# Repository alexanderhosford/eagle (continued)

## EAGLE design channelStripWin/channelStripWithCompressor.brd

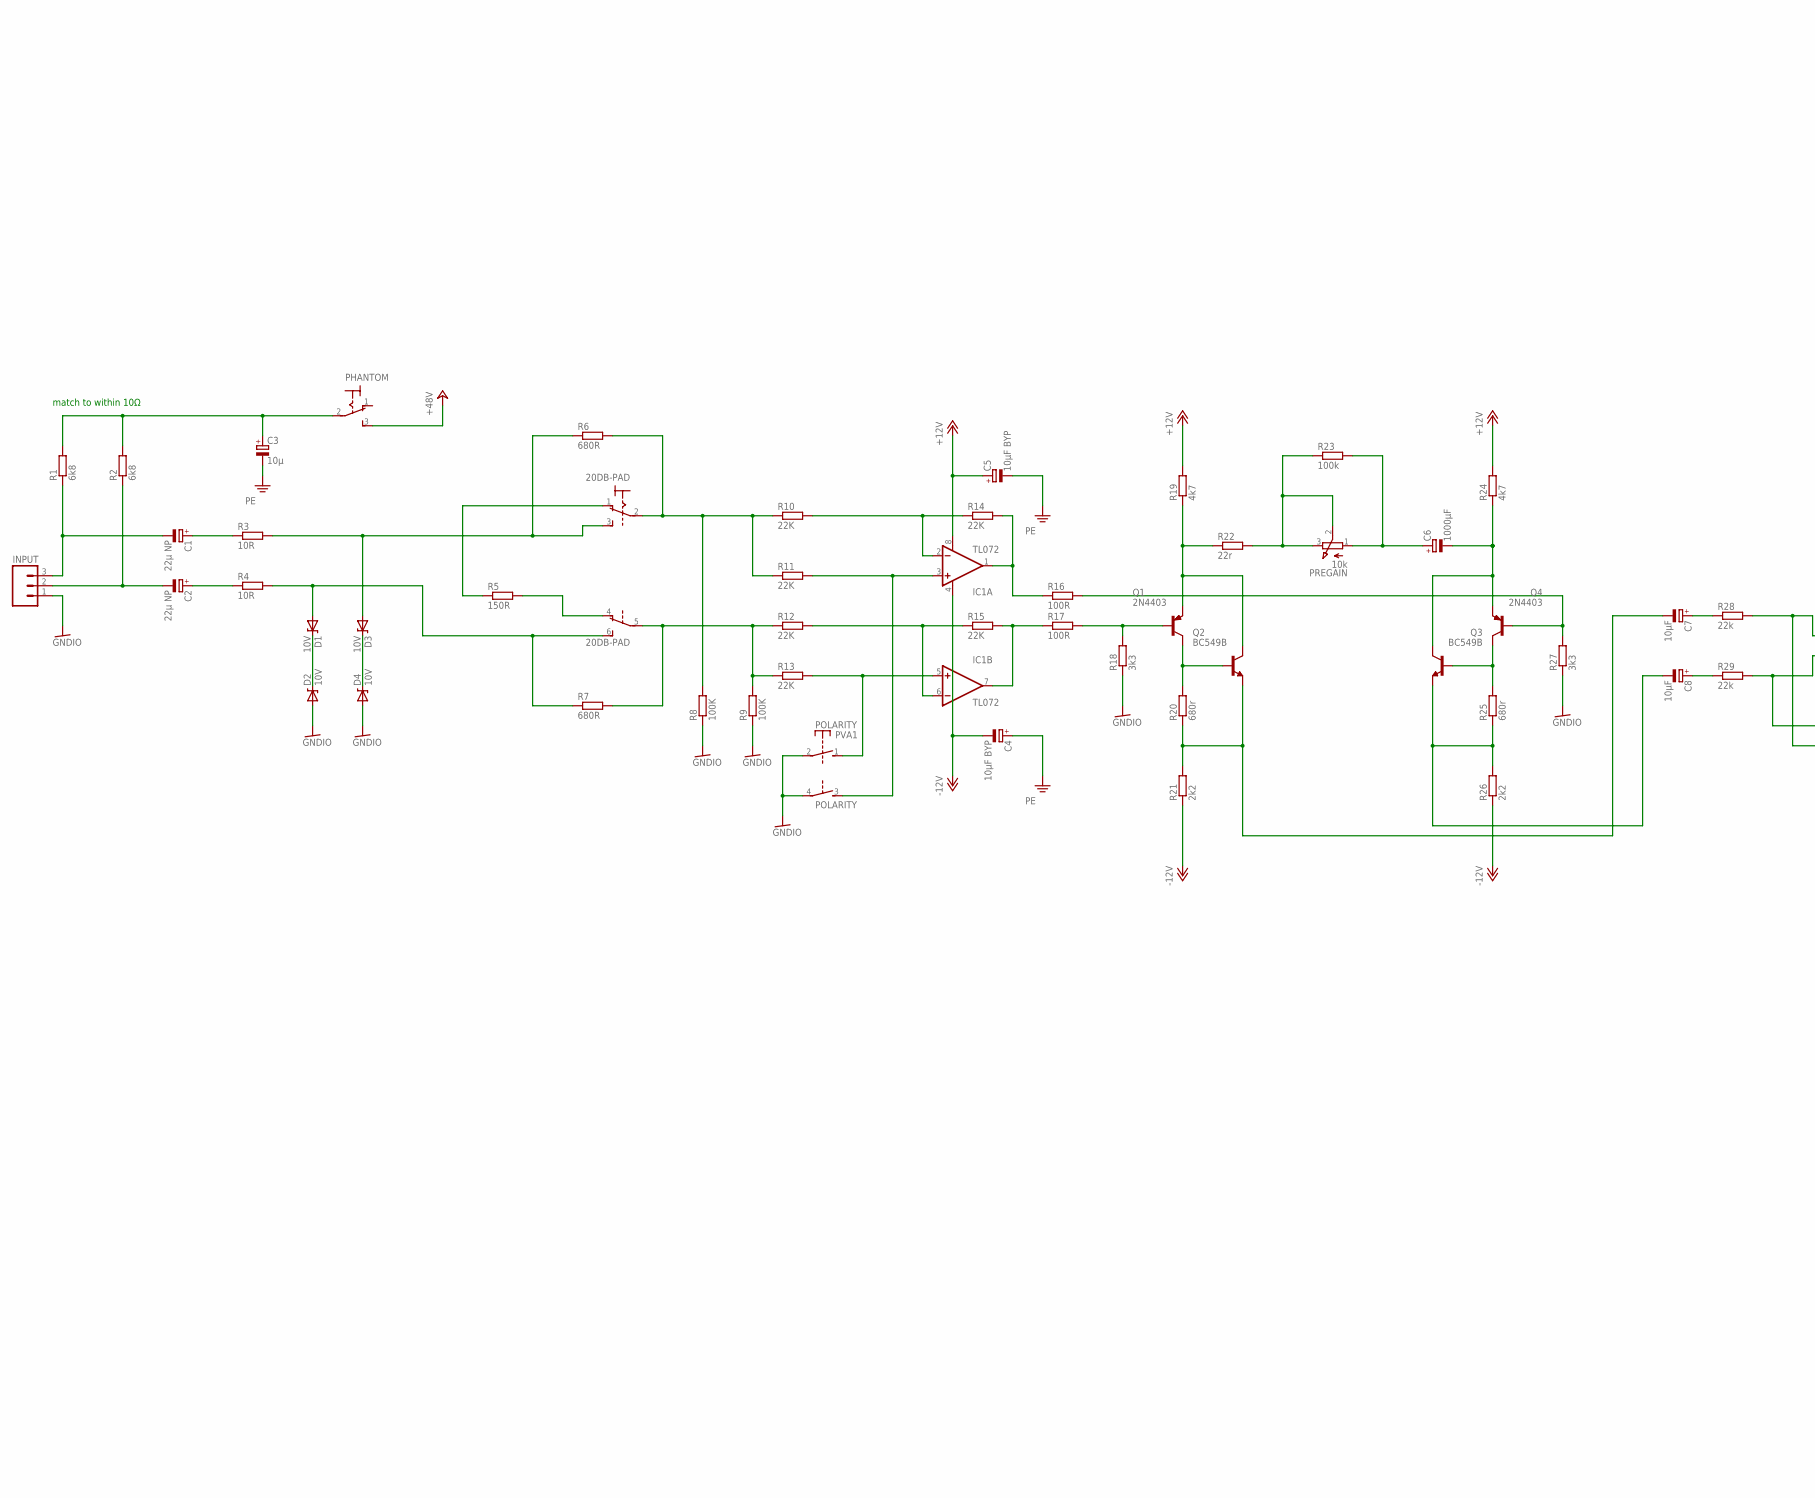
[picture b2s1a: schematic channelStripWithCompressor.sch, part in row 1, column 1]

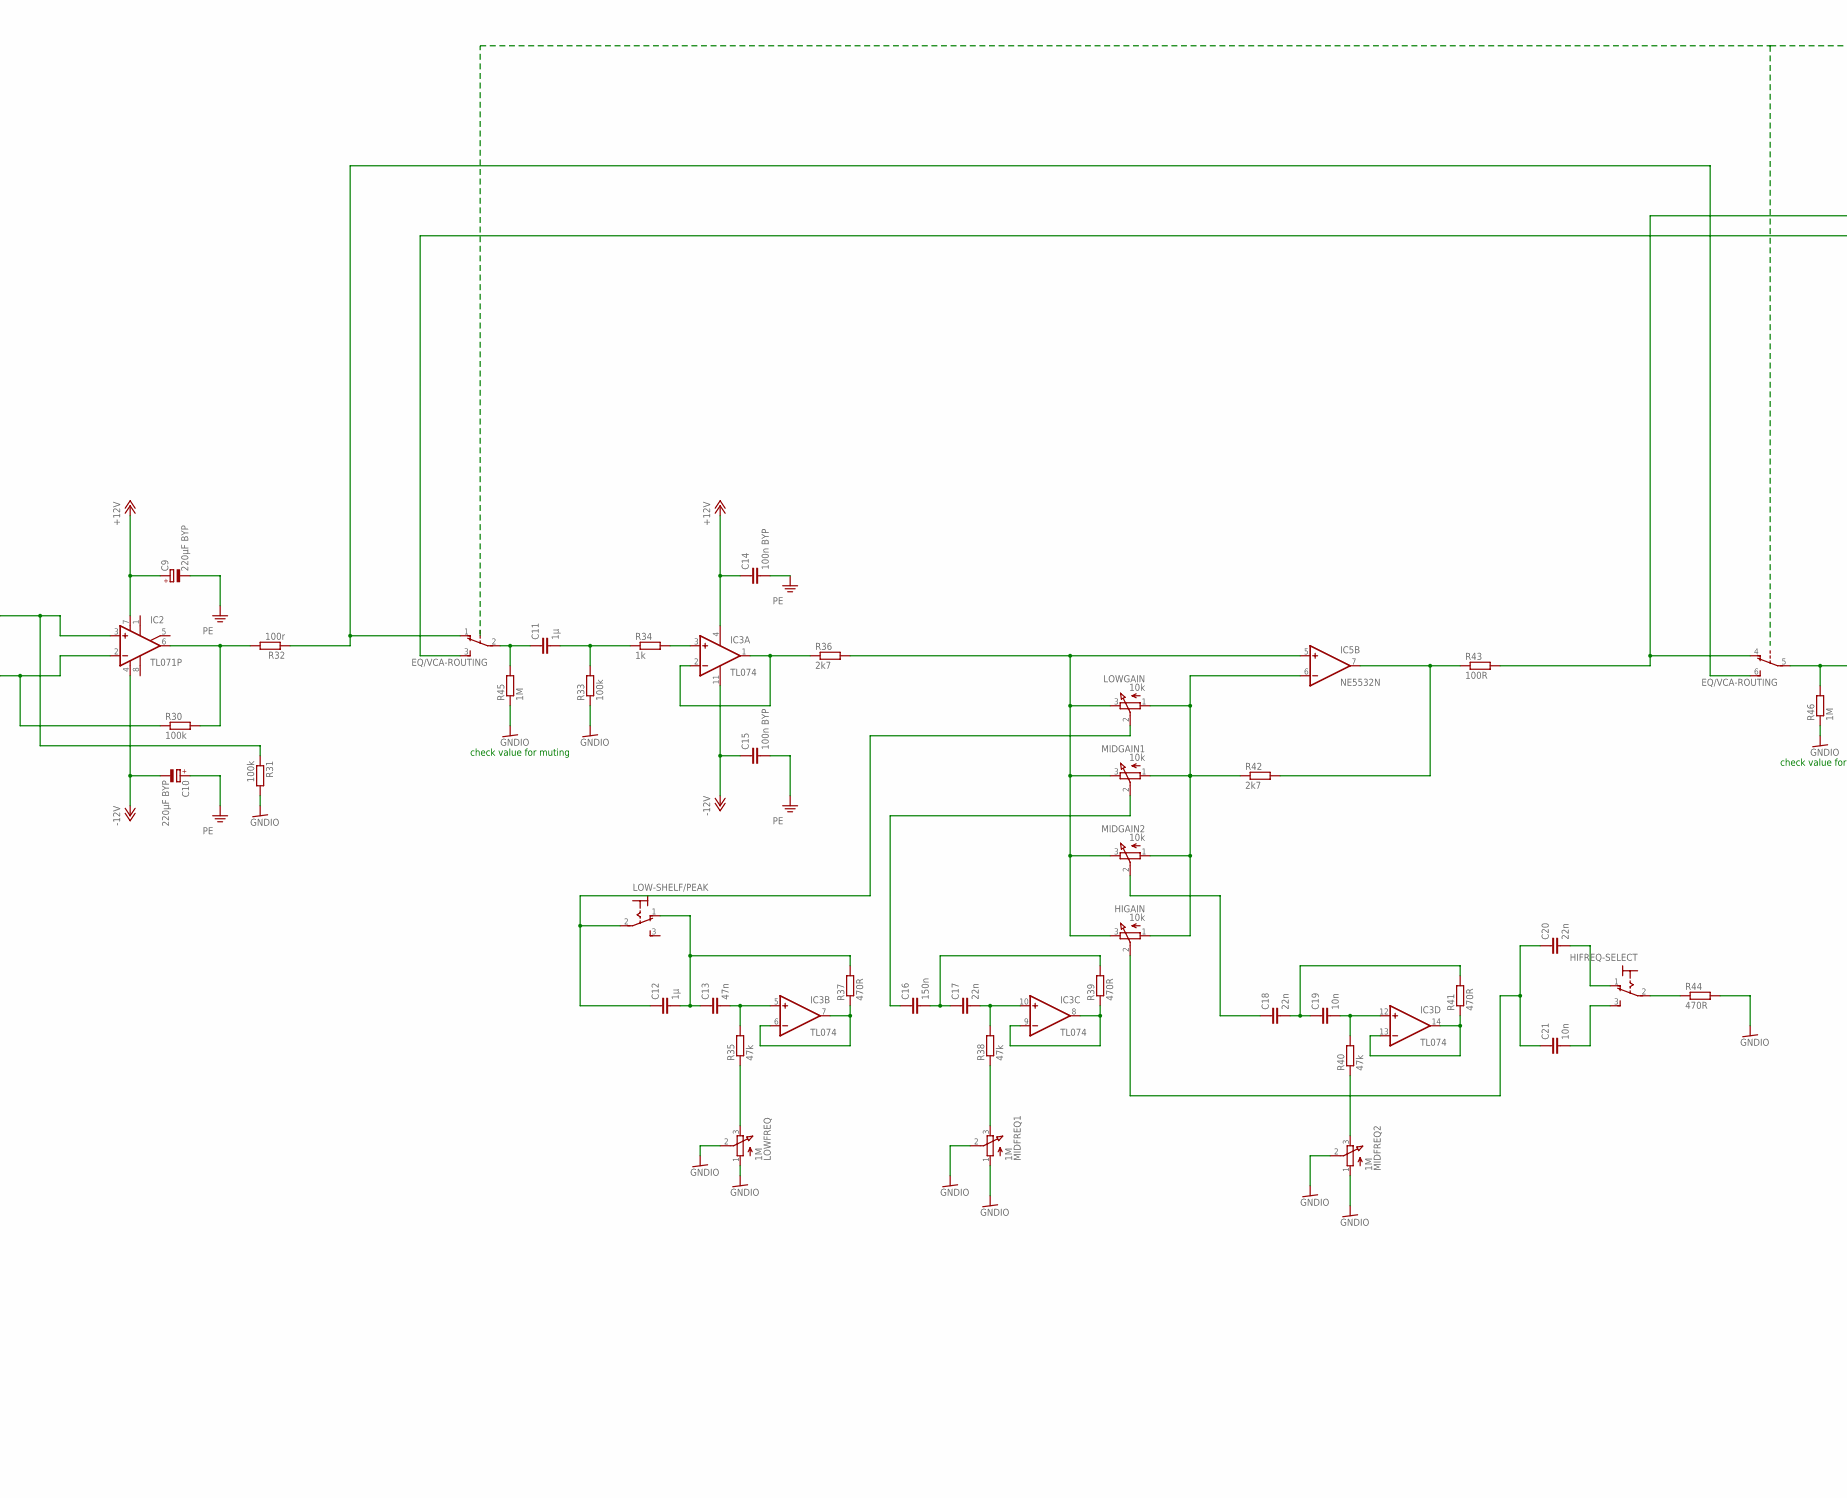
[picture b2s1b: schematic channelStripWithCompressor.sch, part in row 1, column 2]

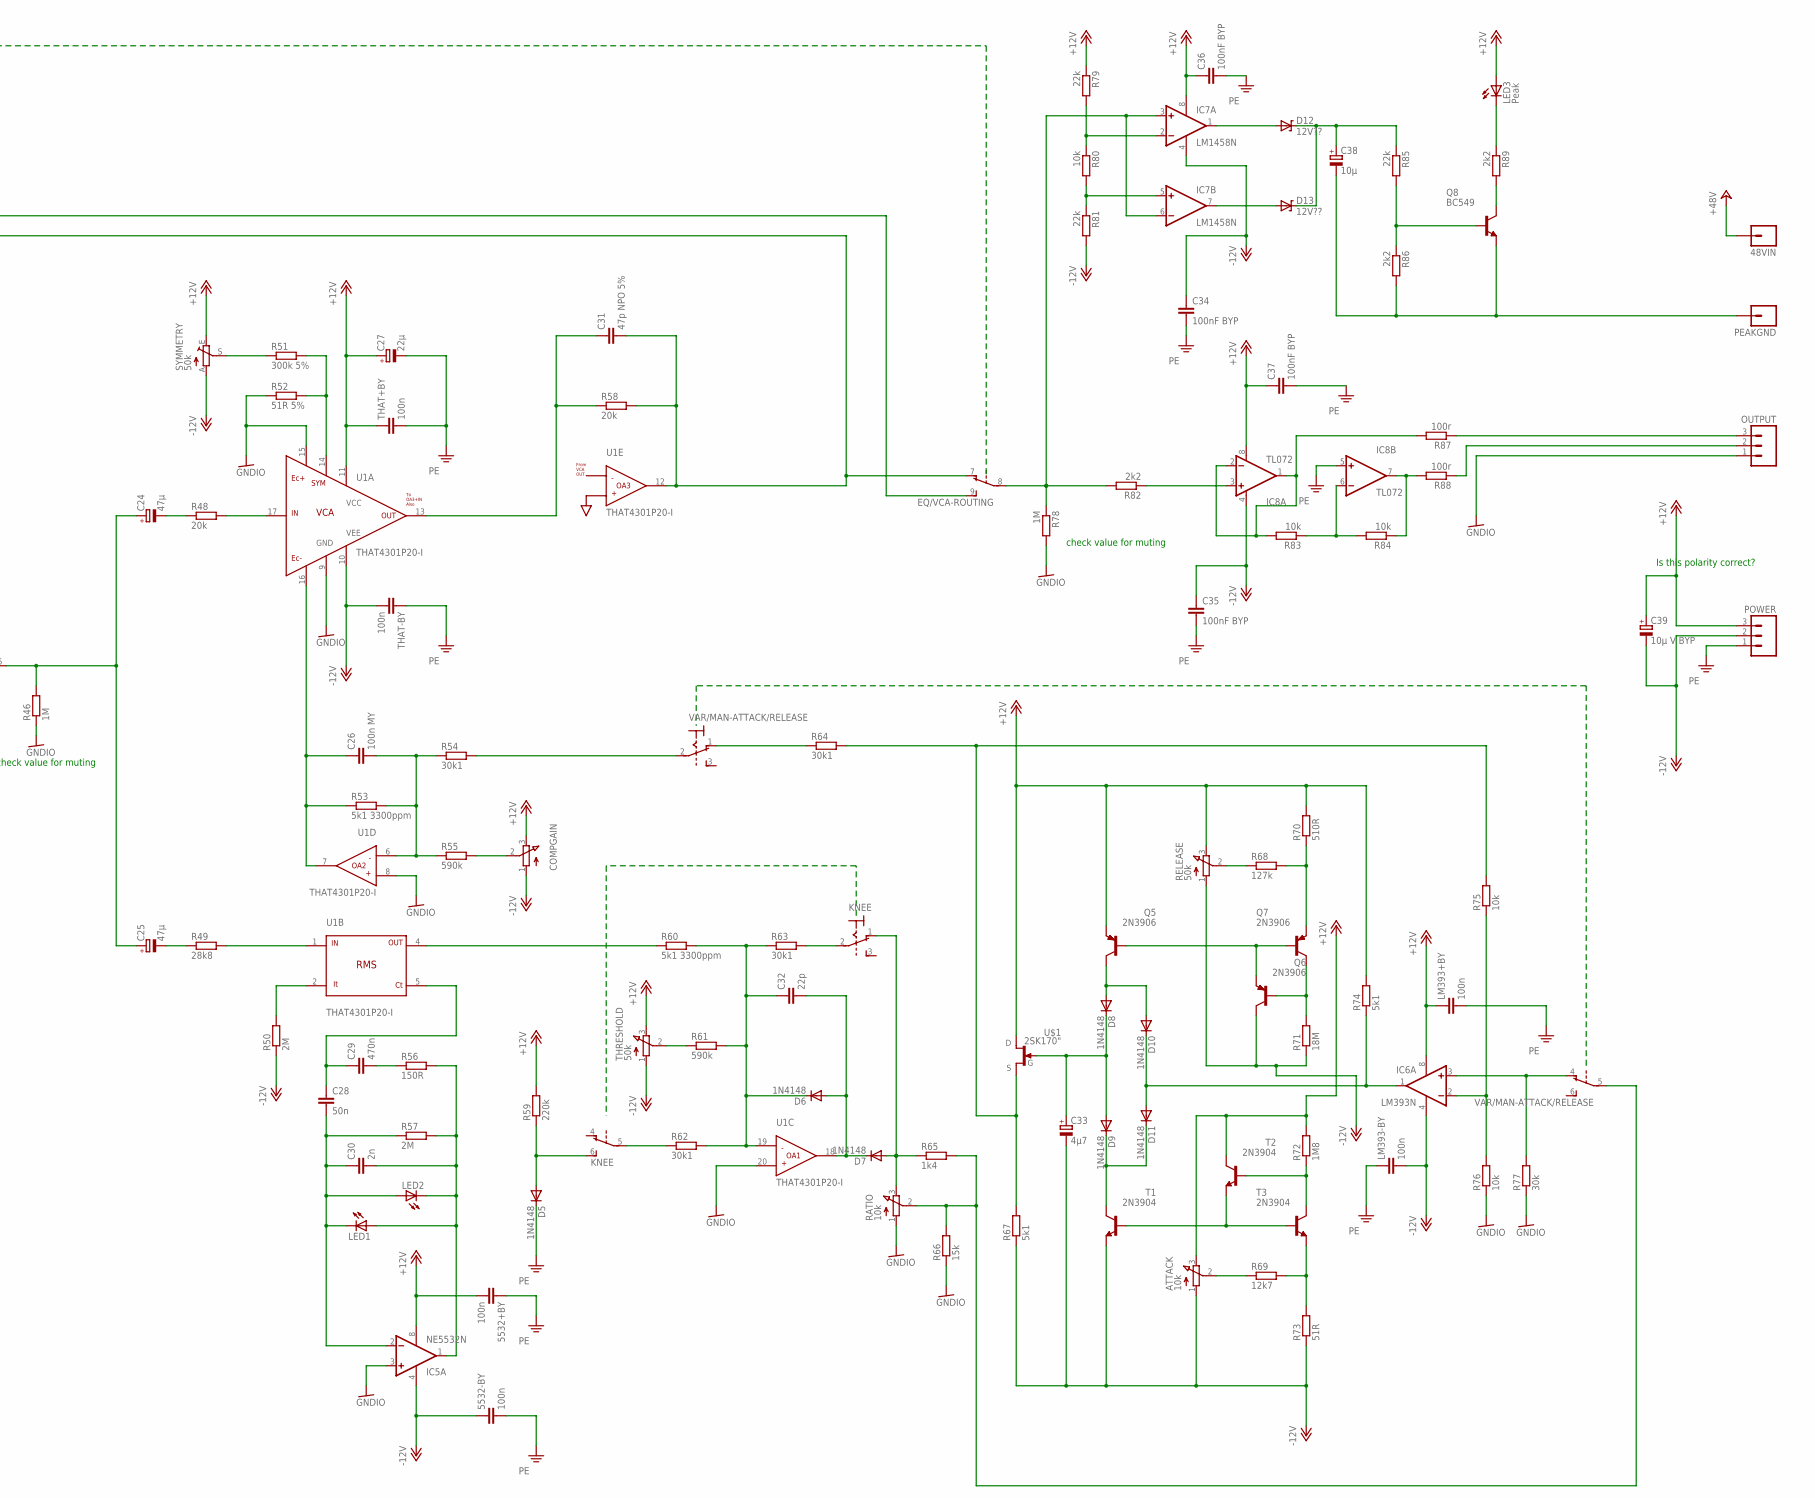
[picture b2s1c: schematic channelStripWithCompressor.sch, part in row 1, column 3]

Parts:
20DB-PAD: 320-938
48VIN: M01PTH; 1X01
5532+BY, 5532-BY: 100n; C050-030X075
ATTACK: 10k; 3RP/1610N
C1, C2: 22µ NP; E2,5-5
C3: 10µ; E2,5-6
C4, C5: 10µF BYP; E2,5-6
C6: 1000µF; E5-10,5
C7, C8: 10µF; E15-5
C9, C10: 220µF BYP; E5-10,5
C11, C12: 1µ; C050-025X075
C13: 47n; C050-025X075
C14, C15: 100n BYP; C050-025X075
C16: 150n; C050-025X075
C17, C18, C20: 22n; C050-025X075
C19, C21: 10n; C050-025X075
C24, C25: 47µ; E2,5-6
C26: 100n MY; C050-030X075
C27: 22µ; E2,5-6
C28: 50n; C050-030X075
C29: 470n; C050-030X075
C30: 2n; C050-030X075
C31: 47p NPO 5%; C050-030X075
C32: 22p; C050-030X075
C33: 4µ7; E2,5-6
C34, C35, C36, C37: 100nF BYP; C050-025X075
C38: 10µ; E2,5-6E
C39: 10µ V BYP; E2,5-6E
COMPGAIN: 3RP/1610N
D1, D2, D3, D4: 10V; DIODE-ZENER
D5, D6, D7, D8, D9, D10, D11: 1N4148; DIODE-1N4148
D12, D13: 12V??; DIODE-ZENER
EQ/VCA-ROUTING: 4PDT-TOGGLE-SWITCH; 4PDT
HIFREQ-SELECT: 320-916
HIGAIN: 10k; 3RP/1610N
IC1, IC8: TL072; DIP08
IC2: TL071P; DIL08
IC3: TL074; DIL14
IC5: NE5532N; DIL08
IC6: LM393N; DIL08
IC7: LM1458N; DIL08
INPUT: M03SCREW; SCREWTERMINAL-3.5MM-3
KNEE: M9040P2
LED1, LED2: LED5MM
LED3: Peak; LED3MM-NS
LM393+BY, LM393-BY: 100n; C050-030X075
LOW-SHELF/PEAK: 320-916
LOWFREQ: 1M; 3RP/1610N
LOWGAIN: 10k; 3RP/1610N
MIDFREQ1, MIDFREQ2: 1M; 3RP/1610N
MIDGAIN1, MIDGAIN2: 10k; 3RP/1610N
OUTPUT: M03SCREW; SCREWTERMINAL-3.5MM-3
PEAKGND: M01PTH_2MM; 1X01_2MM
PHANTOM: 320-916
POLARITY: PVA1; PVA1F
POWER: M03SCREW; SCREWTERMINAL-3.5MM-3
PREGAIN: 10k; 3RP/1610N
Q1, Q4: 2N4403; TO92-BCE
Q2, Q3: BC549B; TO92-EBC
Q5, Q6, Q7: 2N3906; TO92
Q8: BC549; TO92-EBC
R1, R2: 6k8; 0207/7
R3, R4: 10R; 0207/7
R5, R56: 150R; 0207/7
R6, R7: 680R; 0207/7
R8, R9: 100K; 0207/7
R10, R12, R13, R14, R15: 22K; 0207/7
R11: 22K; 0207/10
R16, R17, R43: 100R; 0207/7
R18, R27: 3k3; 0207/7
R19: 4k7; 0207/7
R20, R25: 680r; 0207/7
R21, R26, R82, R86, R89: 2k2; 0207/7
R22: 22r; 0207/7
R23, R30, R31, R33: 100k; 0207/7
R24: 4k7; 0207/10
R28, R29, R79, R81, R85: 22k; 0207/7
R32, R87, R88: 100r; 0207/7
R34: 1k; 0207/7
R35, R38, R40: 47k; 0207/7
R36, R42: 2k7; 0207/7
R37, R39, R41, R44: 470R; 0207/7
R45, R46, R78: 1M; 0207/7
R48, R58: 20k; 0207/7
R49: 28k8; 0207/7
R50, R57: 2M; 0207/7
R51: 300k 5%; 0207/7
R52: 51R 5%; 0207/7
R53, R60: 5k1 3300ppm; 0207/7
R54, R62, R63, R64: 30k1; 0207/7
R55, R61: 590k; 0207/7
R59: 220k; 0207/7
R65: 1k4; 0207/7
R66: 15k; 0207/7
R67, R74: 5k1; 0207/7
R68: 127k; 0207/7
R69: 12k7; 0207/7
R70: 510R; 0207/7
R71: 18M; 0207/7
R72: 1M8; 0207/7
R73: 51R; 0207/7
R75, R76, R80, R83, R84: 10k; 0207/7
R77: 30k; 0207/7
RATIO: 10k; 3RP/1610N
RELEASE: 50k; 3RP/1610N
SYMMETRY: 50k; B64W
T1, T2, T3: 2N3904; TO92
THAT+BY: 100n; C050-030X075
THAT-BY: 100n; C050-030X075
THRESHOLD: 50k; 3RP/1610N
U1: THAT4301P20-I; DIL20
U$1: 2SK170"; TO92-
VAR/MAN-ATTACK/RELEASE: M9040P2

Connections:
+12V: 5532+BY.2, ATTACK.3 (E), C5.+, C9.+, C14.1, C27.+, C36.1, C37.1, C39.+, COMPGAIN.3 (E), IC1.8 (V+), IC2.7 (V+), IC3.4 (V+), IC5.8 (V+), IC6.8 (V+), IC7.8 (V+), IC8.8 (V+), LED3.A, LM393+BY.1, POWER.3, Q5.3 (E), R19.2, R24.2, R59.2, R70.2, R72.2, R74.2, R79.1, RELEASE.3 (E), SYMMETRY.E, T2.1 (C), THAT+BY.1, THRESHOLD.3 (E), U1.11 (VCC), U$1.1 (D)
+48V: 48VIN.1, PHANTOM.3 (S)
-12V: 5532-BY.1, ATTACK.1 (A), C4.-, C10.-, C15.1, C33.-, C34.1, C35.1, C39.-, COMPGAIN.1 (A), IC1.4 (V-), IC2.4 (V-), IC3.11 (V-), IC5.4 (V-), IC6.4 (V-), IC7.4 (V-), IC8.4 (V-), LM393-BY.2, POWER.2, Q6.1 (C), R21.1, R26.1, R50.1, R67.1, R71.1, R73.1, R81.2, RELEASE.1 (A), SYMMETRY.A, T1.3 (E), THAT-BY.2, THRESHOLD.1 (A), U1.10 (VEE)
GNDIO: D2.P$2 (A), D4.P$2 (A), IC5.3 (+IN), INPUT.1, LOWFREQ.1 (A), LOWFREQ.2 (S), MIDFREQ1.1 (A), MIDFREQ1.2 (S), MIDFREQ2.1 (A), MIDFREQ2.2 (S), OUTPUT.1, POLARITY.2, POLARITY.4, R8.1, R9.1, R18.1, R27.1, R31.2, R33.1, R44.2, R45.1, R46.1, R52.1, R66.1, R76.1, R77.1, R78.2, RATIO.1 (A), U1.8 (OA2+IN), U1.9 (GND), U1.15 (EC+), U1.20 (OA1+IN)
unnamed: C18.1, MIDGAIN2.2 (S)
unnamed: IC8.7 (OUT), R84.1, R88.2
unnamed: C7.-, Q2.E, R20.1, R21.2
unnamed: C12.2, C13.1, LOW-SHELF/PEAK.1 (O), R37.2
unnamed: C16.2, C17.1, R39.2
unnamed: C18.2, C19.1, R41.2
unnamed: C20.2, HIFREQ-SELECT.1 (O)
unnamed: C21.2, HIFREQ-SELECT.3 (S)
unnamed: HIFREQ-SELECT.2, R44.1
unnamed: IC3.13 (-IN), IC3.14 (OUT), R41.1
unnamed: C19.2, IC3.12 (+IN), R40.2
unnamed: MIDFREQ1.3 (E), R38.1
unnamed: C11.1, EQ/VCA-ROUTING.2, R45.2
unnamed: C11.2, R33.2, R34.1
unnamed: IC3.3 (+IN), R34.2
unnamed: IC3.1 (OUT), IC3.2 (-IN), R36.1
unnamed: HIGAIN.1 (A), IC5.6 (-IN), LOWGAIN.1 (A), MIDGAIN1.1 (A), MIDGAIN2.1 (A), R42.1
unnamed: IC5.7 (OUT), R42.2, R43.1
unnamed: Q8.B, R85.2, R86.1
unnamed: C1.+, R3.1
unnamed: IC3.6 (-IN), IC3.7 (OUT), R37.1
unnamed: C13.2, IC3.5 (+IN), R35.2
unnamed: LOWFREQ.3 (E), R35.1
unnamed: C12.1, LOW-SHELF/PEAK.2, LOWGAIN.2 (S)
unnamed: IC3.8 (OUT), IC3.9 (-IN), R39.1
unnamed: C2.+, R4.1
unnamed: C17.2, IC3.10 (+IN), R38.2
unnamed: MIDFREQ2.3 (E), R40.1
unnamed: IC7.2 (-IN), R79.2, R80.1
unnamed: C1.-, INPUT.3, R1.1
unnamed: C2.-, INPUT.2, R2.1
unnamed: C3.+, PHANTOM.2, R1.2, R2.2
unnamed: OUTPUT.2, R88.1
unnamed: 20DB-PAD.1 (O), R5.1
unnamed: 20DB-PAD.5, R7.2, R9.2, R12.1, R13.1
unnamed: OUTPUT.3, R87.1
unnamed: IC2.3 (+IN), R28.2, R31.1
unnamed: IC8.6 (-IN), R83.1, R84.2
unnamed: IC8.1 (OUT), IC8.2 (-IN), R83.2, R87.2
unnamed: IC8.3 (+IN), R82.1
unnamed: C20.1, C21.1, HIGAIN.2 (S)
unnamed: C7.+, R28.1
unnamed: IC2.6 (OUT), R30.2, R32.2
unnamed: IC2.2 (-IN), R29.2, R30.1
unnamed: C8.+, R29.1
unnamed: PREGAIN.2 (S), PREGAIN.3 (E), R22.2, R23.1
unnamed: C6.+, PREGAIN.1 (A), R23.2
unnamed: C6.-, Q3.C, Q4.E, R24.1
unnamed: Q1.E, Q2.C, R19.1, R22.1
unnamed: Q3.B, Q4.C, R25.2
unnamed: IC1.1 (OUT), R14.2, R16.1
unnamed: Q1.C, Q2.B, R20.2
unnamed: IC7.5 (+IN), R80.2, R81.1
unnamed: IC1.7 (OUT), R15.2, R17.1
unnamed: C8.-, Q3.E, R25.1, R26.2
unnamed: Q4.B, R16.2, R27.2
unnamed: Q1.B, R17.2, R18.2
unnamed: IC1.6 (-IN), R12.2, R15.1
unnamed: D3.P$1 (C), D4.P$1 (C)
unnamed: IC1.2 (-IN), R10.2, R14.1
unnamed: IC1.5 (+IN), POLARITY.1 (S), R13.2
unnamed: IC1.3 (+IN), POLARITY.3 (S), R11.2
unnamed: 20DB-PAD.2, R6.2, R8.2, R10.1, R11.1
unnamed: D1.P$1 (C), D2.P$1 (C)
unnamed: 20DB-PAD.4 (O), R5.2
unnamed: Q8.C, R89.2
unnamed: 20DB-PAD.6 (S), D1.P$2 (A), R4.2, R7.1
unnamed: C38.+, D12.P$1 (C), D13.P$1 (C), R85.1
unnamed: LED3.K (C), R89.1
unnamed: D12.P$2 (A), IC7.1 (OUT)
unnamed: D13.P$2 (A), IC7.7 (OUT)
unnamed: 20DB-PAD.3 (S), D3.P$2 (A), R3.2, R6.1
unnamed: EQ/VCA-ROUTING.1 (O), EQ/VCA-ROUTING.6 (S), R32.1
unnamed: R48.2, U1.17 (VCA_IN)
unnamed: C24.-, R48.1
unnamed: HIGAIN.3 (E), IC5.5 (+IN), LOWGAIN.3 (E), MIDGAIN1.3 (E), MIDGAIN2.3 (E), R36.2
unnamed: R51.1, SYMMETRY.S
unnamed: R51.2, R52.2, U1.14 (SYM)
unnamed: EQ/VCA-ROUTING.4 (O), EQ/VCA-ROUTING.9 (S), R43.2
unnamed: C31.1, R58.1, U1.13 (VCA_OUT)
unnamed: EQ/VCA-ROUTING.8, IC7.3 (+IN), IC7.6 (-IN), R78.1, R82.2
unnamed: C26.1, R53.1, U1.7 (OA2_OUT), U1.16 (EC-)
unnamed: C16.1, MIDGAIN1.2 (S)
unnamed: C31.2, EQ/VCA-ROUTING.3 (S), EQ/VCA-ROUTING.7 (O), R58.2, U1.12 (OA3_OUT)
unnamed: C26.2, R53.2, R54.1, R55.1, U1.6 (OA2-IN)
unnamed: COMPGAIN.2 (S), R55.2
unnamed: R54.2, VAR/MAN-ATTACK/RELEASE.2
unnamed: C29.2, R56.1
unnamed: C28.1, C29.1, U1.5 (CT)
unnamed: C28.2, C30.1, IC5.2 (-IN), LED1.K (C), LED2.A, R57.1
unnamed: C30.2, IC5.1 (OUT), LED1.A, LED2.K (C), R56.2, R57.2
unnamed: R50.2, U1.2 (IT)
unnamed: R49.2, U1.1 (RMS_IN)
unnamed: C25.-, R49.1
unnamed: R60.1, U1.4 (RMS_OUT)
unnamed: C32.1, D6.C, R60.2, R61.2, R62.2, R63.1, U1.19 (OA1-IN)
unnamed: C32.2, D6.A, D7.C, U1.18 (OA1_OUT)
unnamed: KNEE.2, R63.2
unnamed: R61.1, THRESHOLD.2 (S)
unnamed: KNEE.5, R62.1
unnamed: D5.A, KNEE.6 (S), R59.1
unnamed: R64.1, VAR/MAN-ATTACK/RELEASE.1 (O)
unnamed: D7.A, KNEE.1 (O), R65.1, RATIO.3 (E)
unnamed: R65.2, R66.2, RATIO.2 (S), VAR/MAN-ATTACK/RELEASE.5
unnamed: R64.2, R67.2, R75.2, U$1.3 (S)
unnamed: C33.+, D8.C, D9.A, U$1.2 (G)
unnamed: D9.C, D11.C, T1.1 (C)
unnamed: D8.A, D10.A, Q5.1 (C)
unnamed: D10.C, D11.A, IC6.1 (OUT), R74.1
unnamed: T1.2 (B), T2.3 (E), T3.2 (B)
unnamed: R69.2, R73.2, T3.3 (E)
unnamed: ATTACK.2 (S), R69.1
unnamed: R72.1, T2.2 (B), T3.1 (C)
unnamed: Q5.2 (B), Q6.3 (E), Q7.2 (B)
unnamed: Q6.2 (B), Q7.1 (C), R71.2
unnamed: R68.1, RELEASE.2 (S)
unnamed: Q7.3 (E), R68.2, R70.1
unnamed: IC6.2 (-IN), R75.1, R76.2
unnamed: IC6.3 (+IN), R77.2, VAR/MAN-ATTACK/RELEASE.4 (O)
unnamed: C24.+, C25.+, EQ/VCA-ROUTING.5, R46.2
PE: 5532+BY.1, 5532-BY.2, C3.-, C4.+, C5.-, C9.-, C10.+, C14.2, C15.2, C27.-, C34.2, C35.2, C36.2, C37.2, D5.C, IC8.5 (+IN), LM393+BY.2, LM393-BY.1, POWER.1, THAT+BY.2, THAT-BY.1
PEAKGND: C38.-, PEAKGND.1, Q8.E, R86.2

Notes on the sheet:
Is this polarity correct?
match to within 10Ω
check value for muting

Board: 2 copper layers, 194 parts (0 on the bottom side), 126 nets, no tracks yet.

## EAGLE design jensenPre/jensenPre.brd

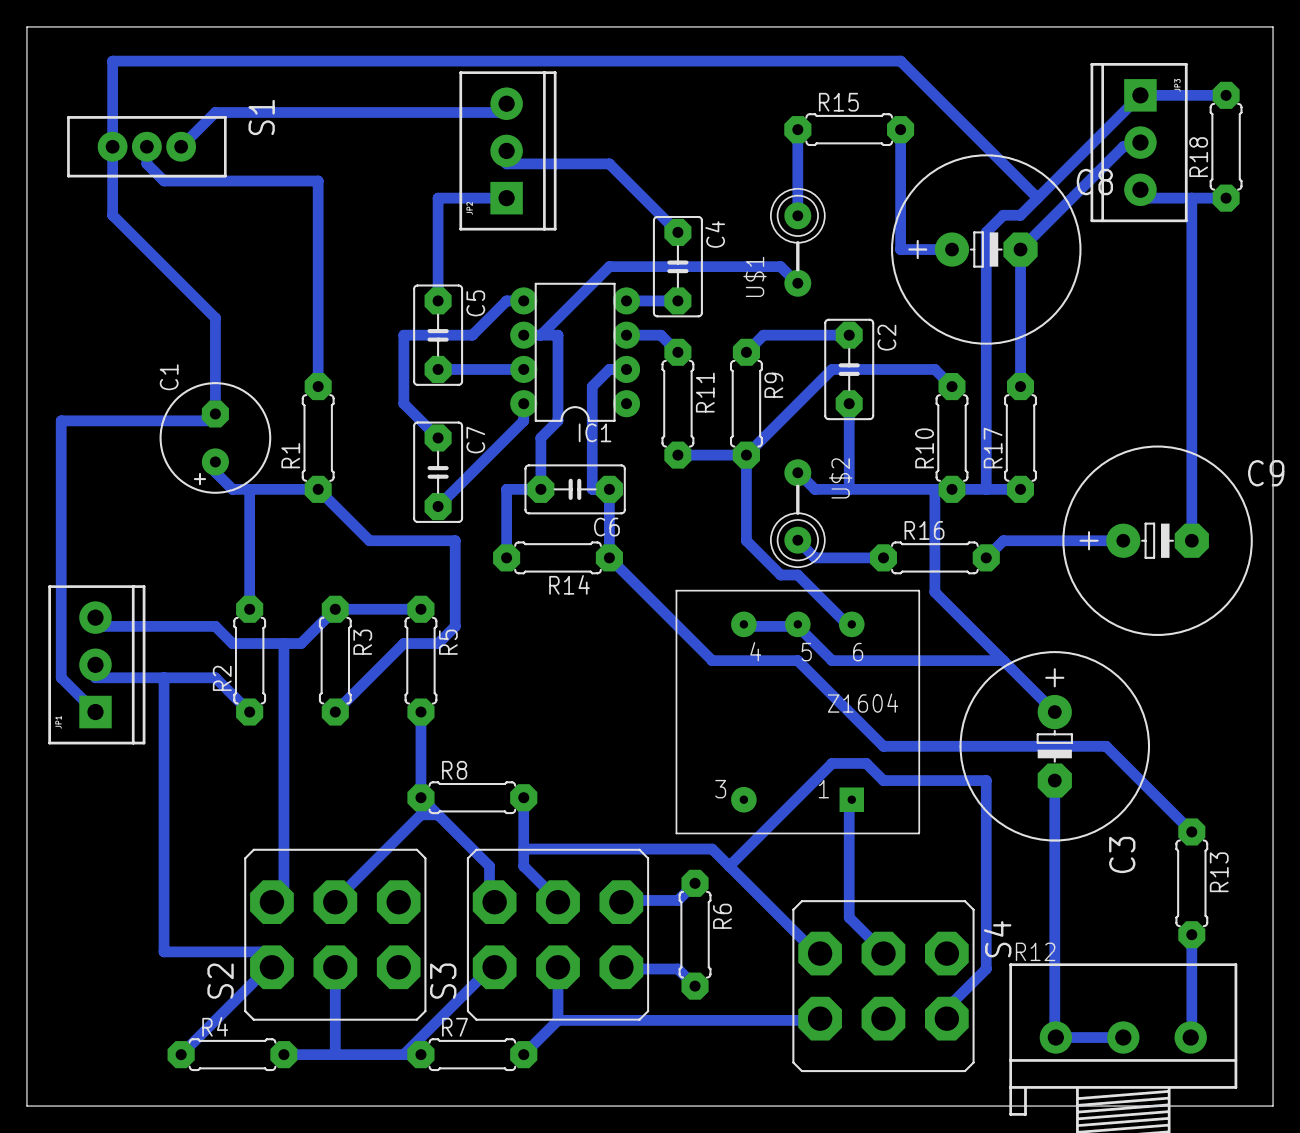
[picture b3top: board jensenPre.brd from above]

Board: 2 copper layers, 92.4 x 80.0 mm, 38 parts (0 on the bottom side), 33 nets.

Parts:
C1: 220µ 63V; E3,5-8
C2: 220p; C050-035X075
C3: 1000µ 35V bp; E5-13
C4, C5: 100n; C050-035X075
C6: 200p; C050-035X075
C7: 22p; C050-035X075
C8, C9: 470µ 35V; E5-13
IC1: NE5534N; DIL08
JP1: INPUT; SCREWTERMINAL-3.5MM-3
JP2: Power; SCREWTERMINAL-3.5MM-3
JP3: Output; SCREWTERMINAL-3.5MM-3
R1: 200R; 0207/7
R2, R3: 6k81; 0207/7
R4, R5: 68r1; 0207/7
R6: 169R; 0207/7
R7, R8: 619R; 0207/7
R9: 12k7; 0207/7
R10: 35k7; 0207/7
R11: 1k; 0207/7
R12: 10k; 3RP/1610N
R13: 100R; 0207/7
R14: 10k; 0207/7
R15, R16: 49R9; 0207/7
R17, R18: 22k1; 0207/7
S1: SWITCH-SPDT
S2, S3, S4: M9040P2
T1: z1604; OEP-Z1604
U$1, U$2: FB

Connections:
5V+: C5.1, JP2.1
5V-: C4.2, IC1.4
48V: JP2.3, S1.1
GND: C1.-, C2.2, C3.+, JP1.1, JP3.1, R10.1, R17.1, R18.2, S1.3, T1.4, T1.5, U$2.P$1
unnamed: C1.+, R1.1, R2.2, R3.2
unnamed: R1.2, S1.2
unnamed: JP1.2, R2.1, R4.1, S2.1
unnamed: JP1.3, R3.1, R5.1, S2.4
unnamed: R4.2, R7.1, S2.2, S3.1
unnamed: R5.2, R8.1, S2.5, S3.4
unnamed: R6.2, S3.3
unnamed: R6.1, S3.6
unnamed: R8.2, S3.5, S4.3, S4.4
unnamed: R7.2, S3.2, S4.1, S4.6
unnamed: S4.2, T1.1
unnamed: S4.5, T1.3
unnamed: R9.2, R10.2, R11.2, T1.6
unnamed: C2.1, R9.1
unnamed: C3.-, R12.1, R12.2
unnamed: R12.3, R13.2
unnamed: C6.1, IC1.2, R13.1, R14.1
unnamed: C6.2, IC1.6, R14.2, U$1.P$1
unnamed: C7.2, IC1.8
unnamed: C7.1, IC1.5
unnamed: R15.1, U$1.P$2
unnamed: C8.+, R15.2
unnamed: C8.-, JP3.2, R17.2
unnamed: IC1.3, R11.1
unnamed: R16.1, U$2.P$2
unnamed: C9.+, R16.2
unnamed: C9.-, JP3.3, R18.1
unnamed: C4.1, JP2.2
unnamed: C5.2, IC1.7

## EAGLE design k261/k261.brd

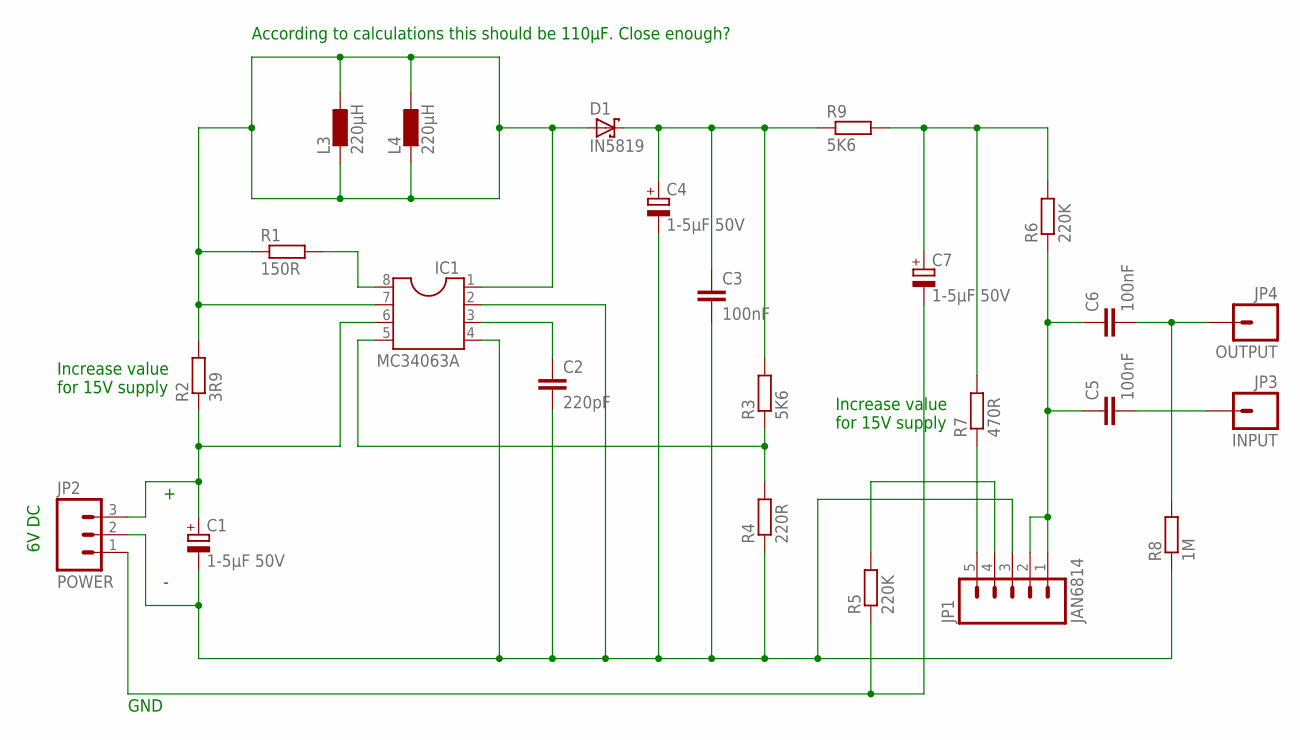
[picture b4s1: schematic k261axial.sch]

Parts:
C1, C4, C7: 1-5µF 50V; E2,5-6E
C2: 220pF; C025-025X050
C3: 100nF; C025-025X050
C5, C6: 100nF; C050-025X075
D1: IN5819; DO41-7.6
IC1: MC34063A; SOCKET-08
JP1: JAN6814; 1X05
JP2: POWER; SCREWTERMINAL-3.5MM-3
JP3: INPUT; 1X01
JP4: OUTPUT; 1X01
L3, L4: 220µH; 0207/10
R1: 150R; 0207/10
R2: 3R9; 0207/10
R3, R9: 5K6; 0207/10
R4: 220R; 0207/10
R5, R6: 220K; 0207/10
R7: 470R; 0207/10
R8: 1M; 0207/10

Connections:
unnamed: C7.-, JP2.1, R5.1
unnamed: C7.+, R6.2, R7.2, R9.2
unnamed: IC1.8, R1.2
unnamed 3: D1.A, IC1.1, IC1.7, L3.1, L3.2, L4.1, L4.2, R1.1, R2.2; also elsewhere on the board
unnamed: C1.+, IC1.6, JP2.3, R2.1
unnamed: C2.1, IC1.3
unnamed: C1.-, C2.2, C3.2, C4.-, IC1.2, IC1.4, JP1.3, JP2.2, R4.1, R8.1
unnamed: C5.1, C6.1, JP1.1, JP1.2, R6.1
unnamed: C6.2, JP4.1, R8.2
unnamed: C3.1, C4.+, D1.C, R3.2, R9.1
unnamed: C5.2, JP3.1
unnamed: JP1.5, R7.1
unnamed: JP1.4, R5.2
unnamed: IC1.5, R3.1, R4.2

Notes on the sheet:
GND
6V DC
According to calculations this should be 110µF. Close enough?
Increase value for 15V supply

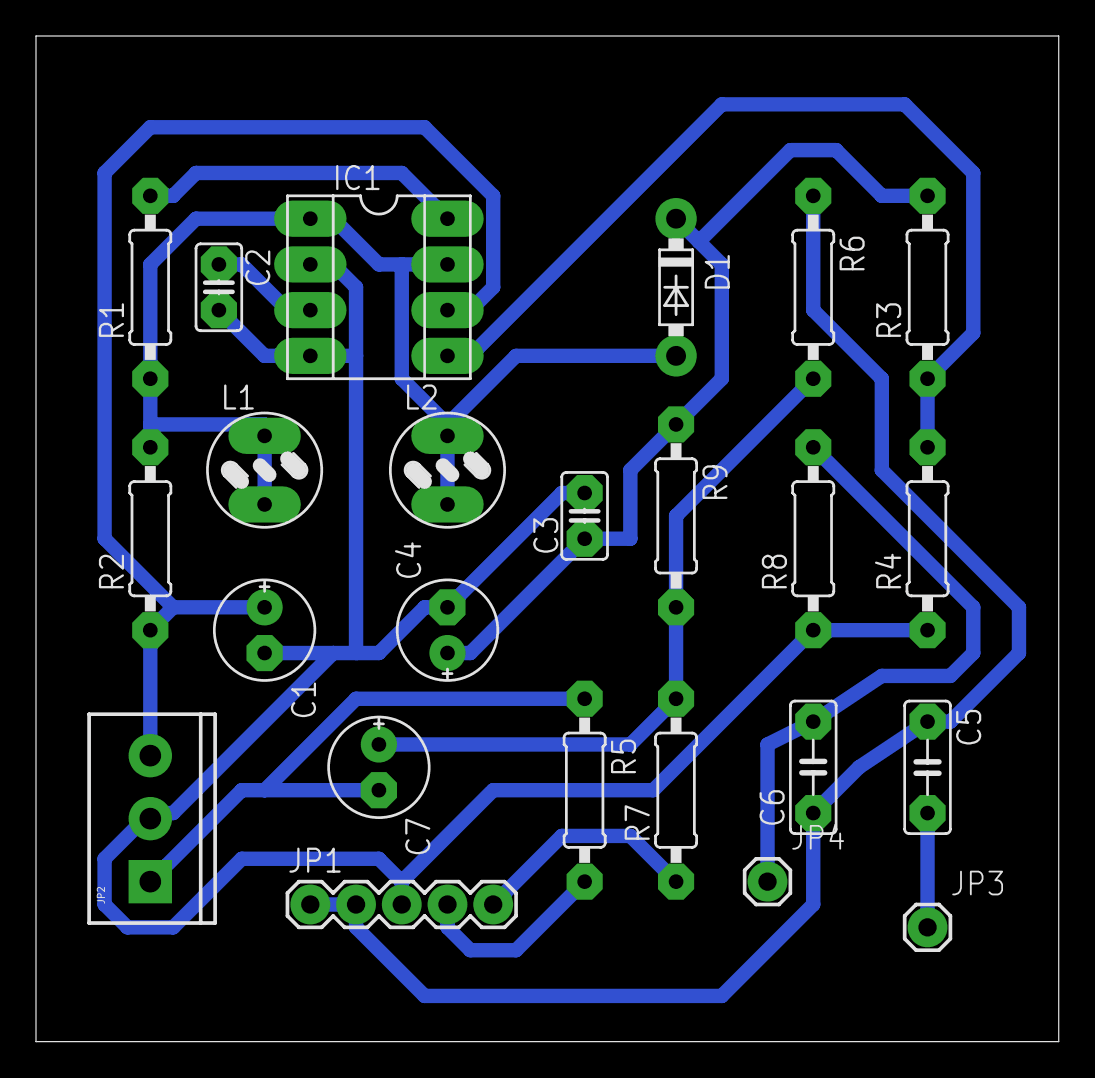
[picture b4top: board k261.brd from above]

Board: 2 copper layers, 56.8 x 55.9 mm, 24 parts (0 on the bottom side), 14 nets.

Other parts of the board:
L1, L2: 220µH; 82114R

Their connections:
unnamed 3: L1.1, L1.2, L2.1, L2.2; also elsewhere on the board
